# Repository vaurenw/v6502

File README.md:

A single-board computer built around a W65C02S 6502 CPU. It uses a Lattice ICE40HX4K FPGA as a custom chipset. The FPGA handles video, audio, keyboard, storage, and address decoding.

---

## Hardware

| Part | What it does |
|------|-------------|
| W65C02S | Main CPU, socketed |
| ICE40HX4K | FPGA chipset for video, audio, IO |
| 62256 SRAM | 32K RAM, socketed |
| AT28C256 EEPROM | 32K ROM, socketed |
| SN74LVC8T245 × 2 | 5V ↔ 3.3V level shifters for the data bus |
| FT230XS | USB-to-UART bridge for debug |
| MicroSD slot | SPI storage via FPGA |
| VGA connector | 640×480 @ 60Hz, resistor ladder DAC |
| PS/2 connector | Keyboard input, decoded in FPGA |

---

## Memory map

```
0x0000 – 0x7FFF   RAM
0x8000 – 0x8FFF   FPGA registers / VRAM window
0x9000 – 0xBFFF   Expansion
0xC000 – 0xFFFF   ROM
```

---

## Schematic sheets

```
V-6502.kicad_sch       root
├── Power.kicad_sch    USB-C, TVS, LDOs, decoupling
├── CPU.kicad_sch      W65C02S, clock, reset
├── Memory.kicad_sch   SRAM, EEPROM
├── LevelShift.kicad_sch   SN74LVC8T245 data bus bridges
├── FPGA.kicad_sch     ICE40HX4K, config flash, oscillator
├── VGA.kicad_sch      DE-15, RGB resistor ladder
├── PS2.kicad_sch      Mini-DIN-6, ESD, pull-ups
├── SD.kicad_sch       MicroSD slot, SPI
├── Audio.kicad_sch    Buzzer, 3.5mm jack
└── Debug.kicad_sch    FT230XS, UART header, test points
```

---

## Status

**Schematic done.** ERC passes clean.

**PCB layout in progress.** The power section is partially routed.

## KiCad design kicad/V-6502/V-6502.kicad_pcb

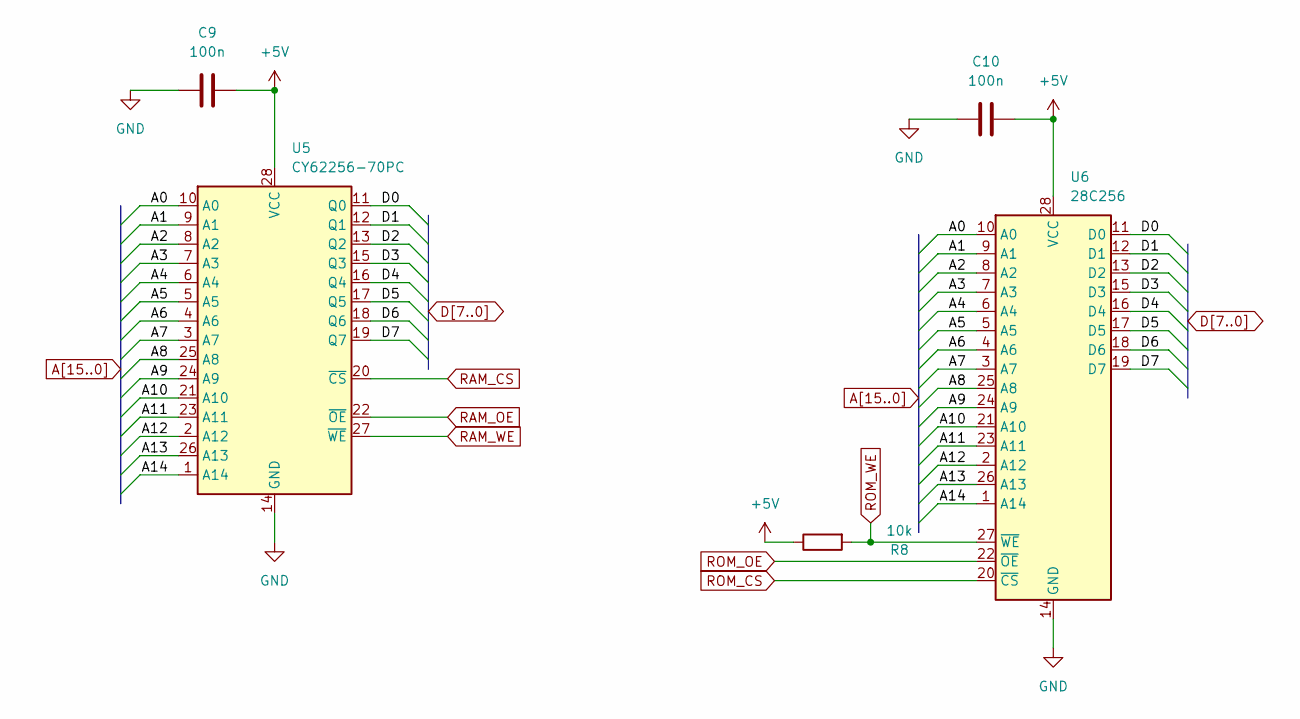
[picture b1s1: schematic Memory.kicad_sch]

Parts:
C9, C10: 100n; C_0805_2012Metric
R8: 10k; R_0402_1005Metric
U5: CY62256-70PC; DIP-28_W15.24mm_Socket
U6: 28C256; DIP-28_W15.24mm_Socket

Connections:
+5V: C9.2, C10.2, R8.1, U5.28 (VCC), U6.28 (VCC); also elsewhere on the board
A0: U5.10 (A0), U6.10 (A0); also elsewhere on the board
A1: U5.9 (A1), U6.9 (A1); also elsewhere on the board
A2: U5.8 (A2), U6.8 (A2); also elsewhere on the board
A3: U5.7 (A3), U6.7 (A3); also elsewhere on the board
A4: U5.6 (A4), U6.6 (A4); also elsewhere on the board
A5: U5.5 (A5), U6.5 (A5); also elsewhere on the board
A6: U5.4 (A6), U6.4 (A6); also elsewhere on the board
A7: U5.3 (A7), U6.3 (A7); also elsewhere on the board
A8: U5.25 (A8), U6.25 (A8); also elsewhere on the board
A9: U5.24 (A9), U6.24 (A9); also elsewhere on the board
A10: U5.21 (A10), U6.21 (A10); also elsewhere on the board
A11: U5.23 (A11), U6.23 (A11); also elsewhere on the board
A12: U5.2 (A12), U6.2 (A12); also elsewhere on the board
A13: U5.26 (A13), U6.26 (A13); also elsewhere on the board
A14: U5.1 (A14), U6.1 (A14); also elsewhere on the board
D0: U5.11 (Q0), U6.11 (D0); also elsewhere on the board
D1: U5.12 (Q1), U6.12 (D1); also elsewhere on the board
D2: U5.13 (Q2), U6.13 (D2); also elsewhere on the board
D3: U5.15 (Q3), U6.15 (D3); also elsewhere on the board
D4: U5.16 (Q4), U6.16 (D4); also elsewhere on the board
D5: U5.17 (Q5), U6.17 (D5); also elsewhere on the board
D6: U5.18 (Q6), U6.18 (D6); also elsewhere on the board
D7: U5.19 (Q7), U6.19 (D7); also elsewhere on the board
GND: C9.1, C10.1, U5.14 (GND), U6.14 (GND); also elsewhere on the board
RAM_CS: U5.20 (~CS); also elsewhere on the board
RAM_OE: U5.22 (~OE); also elsewhere on the board
RAM_WE: U5.27 (~WE); also elsewhere on the board
ROM_CS: U6.20 (~CS); also elsewhere on the board
ROM_OE: U6.22 (~OE); also elsewhere on the board
ROM_WE: R8.2, U6.27 (~WE); also elsewhere on the board

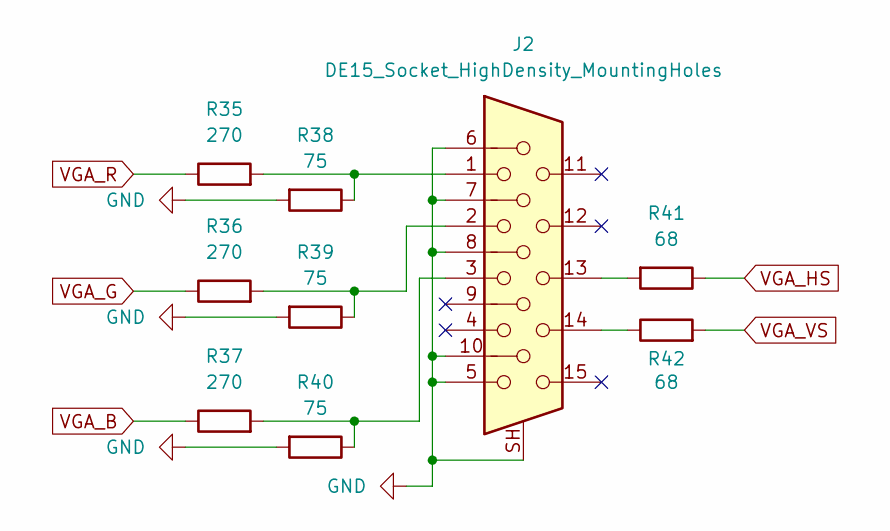
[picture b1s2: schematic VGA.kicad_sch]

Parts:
J2: DE15_Socket_HighDensity_MountingHoles; DSUB-15-HD_Socket_Vertical_P2.29x1.98mm_MountingHoles
R35, R36, R37: 270; R_0402_1005Metric
R38, R39, R40: 75; R_0402_1005Metric
R41, R42: 68; R_0402_1005Metric

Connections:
GND: J2.5, J2.6, J2.7, J2.8, J2.10, J2.SH, R38.2, R39.2, R40.2; also elsewhere on the board
unnamed: J2.1, R35.2, R38.1
unnamed: J2.2, R36.2, R39.1
unnamed: J2.3, R37.2, R40.1
unnamed: J2.13, R41.2
unnamed: J2.14, R42.1
VGA_B: R37.1; also elsewhere on the board
VGA_G: R36.1; also elsewhere on the board
VGA_HS: R41.1; also elsewhere on the board
VGA_R: R35.1; also elsewhere on the board
VGA_VS: R42.2; also elsewhere on the board

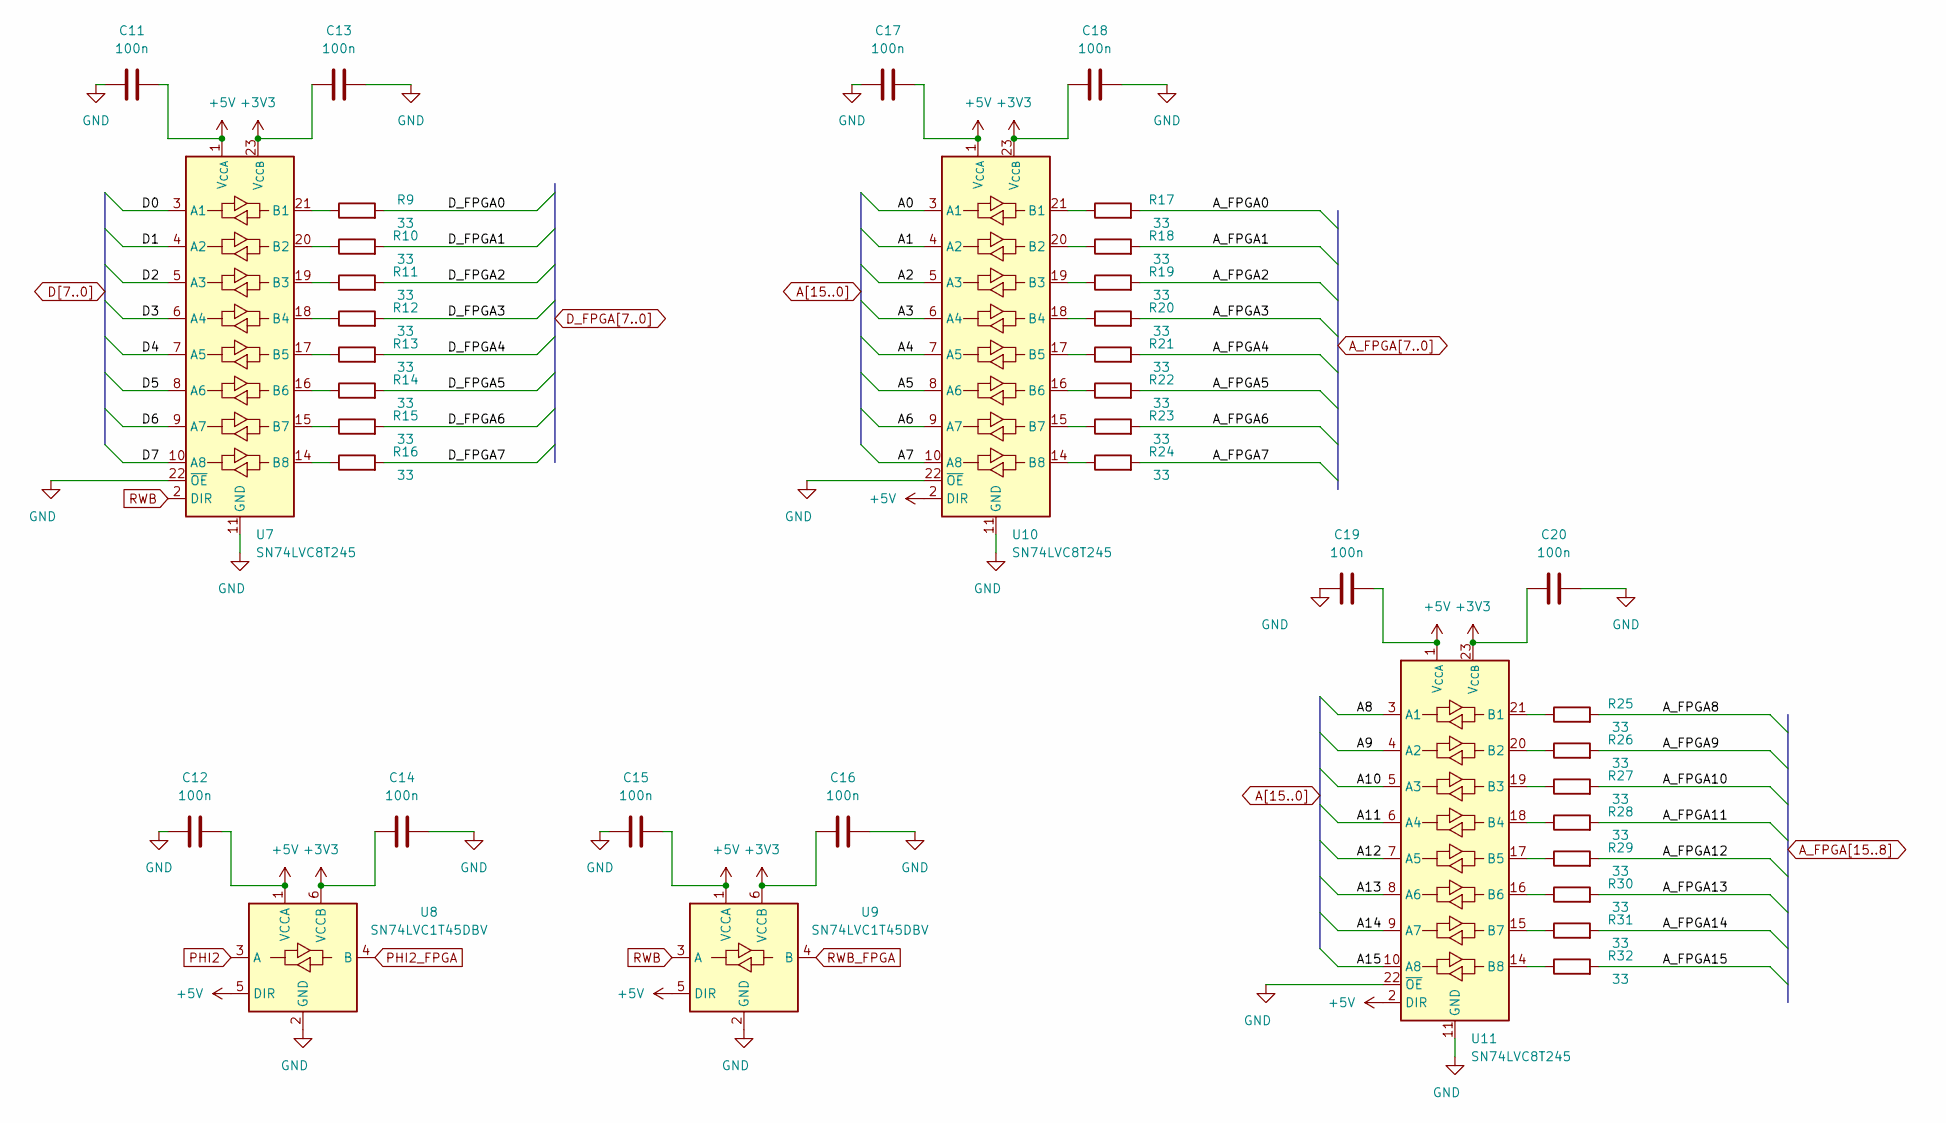
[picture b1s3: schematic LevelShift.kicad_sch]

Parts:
C11, C12, C13, C14, C15, C16, C17, C18, C19, C20: 100n; C_0805_2012Metric
R9, R10, R11, R12, R13, R14, R15, R16, R17, R18, R19, R20, R21, R22, R23, R24, R25, R26, R27, R28, R29, R30, R31, R32: 33; R_0402_1005Metric
U7, U10, U11: SN74LVC8T245; TSSOP-24_4.4x7.8mm_P0.65mm
U8, U9: SN74LVC1T45DBV; SOT-23-6

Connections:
+3V3: C13.2, C14.2, C16.2, C18.2, C20.2, U7.23 (V_{CCB}), U7.24 (V_{CCB}), U8.6 (VCCB), U9.6 (VCCB), U10.23 (V_{CCB}), U10.24 (V_{CCB}), U11.23 (V_{CCB}), U11.24 (V_{CCB}); also elsewhere on the board
+5V: C11.2, C12.2, C15.2, C17.2, C19.2, U7.1 (V_{CCA}), U8.1 (VCCA), U8.5 (DIR), U9.1 (VCCA), U9.5 (DIR), U10.1 (V_{CCA}), U10.2 (DIR), U11.1 (V_{CCA}), U11.2 (DIR); also elsewhere on the board
A0: U10.3 (A1); also elsewhere on the board
A1: U10.4 (A2); also elsewhere on the board
A2: U10.5 (A3); also elsewhere on the board
A3: U10.6 (A4); also elsewhere on the board
A4: U10.7 (A5); also elsewhere on the board
A5: U10.8 (A6); also elsewhere on the board
A6: U10.9 (A7); also elsewhere on the board
A7: U10.10 (A8); also elsewhere on the board
A8: U11.3 (A1); also elsewhere on the board
A9: U11.4 (A2); also elsewhere on the board
A10: U11.5 (A3); also elsewhere on the board
A11: U11.6 (A4); also elsewhere on the board
A12: U11.7 (A5); also elsewhere on the board
A13: U11.8 (A6); also elsewhere on the board
A14: U11.9 (A7); also elsewhere on the board
A15: U11.10 (A8); also elsewhere on the board
A_FPGA0: R17.2; also elsewhere on the board
A_FPGA1: R18.2; also elsewhere on the board
A_FPGA2: R19.2; also elsewhere on the board
A_FPGA3: R20.2; also elsewhere on the board
A_FPGA4: R21.2; also elsewhere on the board
A_FPGA5: R22.2; also elsewhere on the board
A_FPGA6: R23.2; also elsewhere on the board
A_FPGA7: R24.2; also elsewhere on the board
A_FPGA8: R25.2; also elsewhere on the board
A_FPGA9: R26.2; also elsewhere on the board
A_FPGA10: R27.2; also elsewhere on the board
A_FPGA11: R28.2; also elsewhere on the board
A_FPGA12: R29.2; also elsewhere on the board
A_FPGA13: R30.2; also elsewhere on the board
A_FPGA14: R31.2; also elsewhere on the board
A_FPGA15: R32.2; also elsewhere on the board
D0: U7.3 (A1); also elsewhere on the board
D1: U7.4 (A2); also elsewhere on the board
D2: U7.5 (A3); also elsewhere on the board
D3: U7.6 (A4); also elsewhere on the board
D4: U7.7 (A5); also elsewhere on the board
D5: U7.8 (A6); also elsewhere on the board
D6: U7.9 (A7); also elsewhere on the board
D7: U7.10 (A8); also elsewhere on the board
D_FPGA0: R9.2; also elsewhere on the board
D_FPGA1: R10.2; also elsewhere on the board
D_FPGA2: R11.2; also elsewhere on the board
D_FPGA3: R12.2; also elsewhere on the board
D_FPGA4: R13.2; also elsewhere on the board
D_FPGA5: R14.2; also elsewhere on the board
D_FPGA6: R15.2; also elsewhere on the board
D_FPGA7: R16.2; also elsewhere on the board
GND: C11.1, C12.1, C13.1, C14.1, C15.1, C16.1, C17.1, C18.1, C19.1, C20.1, U7.11 (GND), U7.12 (GND), U7.13 (GND), U7.22 (~OE), U8.2 (GND), U9.2 (GND), U10.11 (GND), U10.12 (GND), U10.13 (GND), U10.22 (~OE), U11.11 (GND), U11.12 (GND), U11.13 (GND), U11.22 (~OE); also elsewhere on the board
unnamed: R9.1, U7.21 (B1)
unnamed: R10.1, U7.20 (B2)
unnamed: R11.1, U7.19 (B3)
unnamed: R12.1, U7.18 (B4)
unnamed: R13.1, U7.17 (B5)
unnamed: R14.1, U7.16 (B6)
unnamed: R15.1, U7.15 (B7)
unnamed: R16.1, U7.14 (B8)
unnamed: R17.1, U10.21 (B1)
unnamed: R18.1, U10.20 (B2)
unnamed: R19.1, U10.19 (B3)
unnamed: R20.1, U10.18 (B4)
unnamed: R21.1, U10.17 (B5)
unnamed: R22.1, U10.16 (B6)
unnamed: R23.1, U10.15 (B7)
unnamed: R24.1, U10.14 (B8)
unnamed: R25.1, U11.21 (B1)
unnamed: R26.1, U11.20 (B2)
unnamed: R27.1, U11.19 (B3)
unnamed: R28.1, U11.18 (B4)
unnamed: R29.1, U11.17 (B5)
unnamed: R30.1, U11.16 (B6)
unnamed: R31.1, U11.15 (B7)
unnamed: R32.1, U11.14 (B8)
PHI2: U8.3 (A); also elsewhere on the board
PHI2_FPGA: U8.4 (B); also elsewhere on the board
RWB: U7.2 (DIR), U9.3 (A); also elsewhere on the board
RWB_FPGA: U9.4 (B); also elsewhere on the board

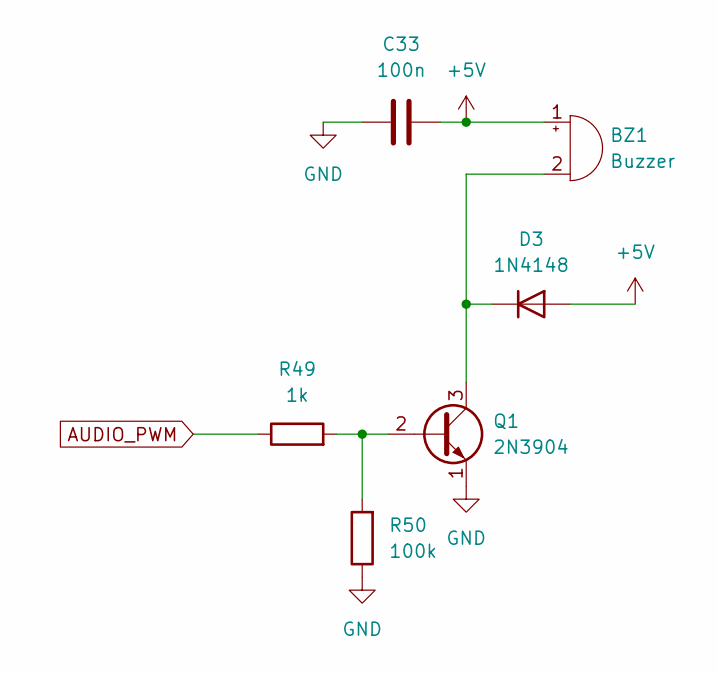
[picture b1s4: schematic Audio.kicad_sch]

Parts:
BZ1: Buzzer; Buzzer_15x7.5RM7.6
C33: 100n; C_0805_2012Metric
D3: 1N4148; D_DO-35_SOD27_P7.62mm_Horizontal
Q1: 2N3904; TO-92_Inline
R49: 1k; R_0402_1005Metric
R50: 100k; R_0402_1005Metric

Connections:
+5V: BZ1.1 (+), C33.2, D3.2 (A); also elsewhere on the board
AUDIO_PWM: R49.1; also elsewhere on the board
GND: C33.1, Q1.1 (E), R50.1; also elsewhere on the board
unnamed: BZ1.2 (-), D3.1 (K), Q1.3 (C)
unnamed: Q1.2 (B), R49.2, R50.2

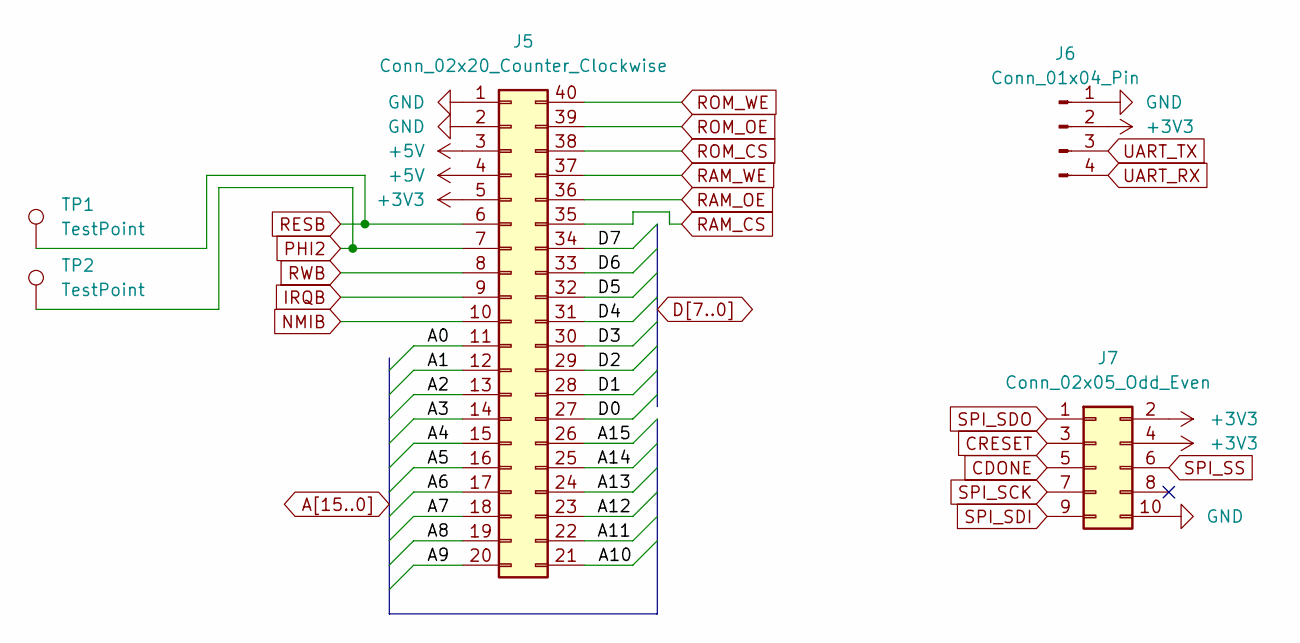
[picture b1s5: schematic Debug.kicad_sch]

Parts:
J5: Conn_02x20_Counter_Clockwise; PinSocket_2x20_P2.54mm_Vertical
J6: Conn_01x04_Pin; PinHeader_1x04_P2.54mm_Vertical
J7: Conn_02x05_Odd_Even; IDC-Header_2x05_P2.54mm_Vertical
TP1, TP2: TestPoint; TestPoint_Pad_D1.0mm

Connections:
+3V3: J5.5, J6.2, J7.2, J7.4; also elsewhere on the board
+5V: J5.3, J5.4; also elsewhere on the board
A0: J5.11; also elsewhere on the board
A1: J5.12; also elsewhere on the board
A2: J5.13; also elsewhere on the board
A3: J5.14; also elsewhere on the board
A4: J5.15; also elsewhere on the board
A5: J5.16; also elsewhere on the board
A6: J5.17; also elsewhere on the board
A7: J5.18; also elsewhere on the board
A8: J5.19; also elsewhere on the board
A9: J5.20; also elsewhere on the board
A10: J5.21; also elsewhere on the board
A11: J5.22; also elsewhere on the board
A12: J5.23; also elsewhere on the board
A13: J5.24; also elsewhere on the board
A14: J5.25; also elsewhere on the board
A15: J5.26; also elsewhere on the board
CDONE: J7.5; also elsewhere on the board
CRESET: J7.3; also elsewhere on the board
D0: J5.27; also elsewhere on the board
D1: J5.28; also elsewhere on the board
D2: J5.29; also elsewhere on the board
D3: J5.30; also elsewhere on the board
D4: J5.31; also elsewhere on the board
D5: J5.32; also elsewhere on the board
D6: J5.33; also elsewhere on the board
D7: J5.34; also elsewhere on the board
GND: J5.1, J5.2, J6.1, J7.10; also elsewhere on the board
IRQB: J5.9; also elsewhere on the board
NMIB: J5.10; also elsewhere on the board
PHI2: J5.7, TP2.1 (1_1); also elsewhere on the board
RAM_CS: J5.35; also elsewhere on the board
RAM_OE: J5.36; also elsewhere on the board
RAM_WE: J5.37; also elsewhere on the board
RESB: J5.6, TP1.1 (1_1); also elsewhere on the board
ROM_CS: J5.38; also elsewhere on the board
ROM_OE: J5.39; also elsewhere on the board
ROM_WE: J5.40; also elsewhere on the board
RWB: J5.8; also elsewhere on the board
SPI_SCK: J7.7; also elsewhere on the board
SPI_SDI: J7.9; also elsewhere on the board
SPI_SDO: J7.1; also elsewhere on the board
SPI_SS: J7.6; also elsewhere on the board
UART_RX: J6.4; also elsewhere on the board
UART_TX: J6.3; also elsewhere on the board

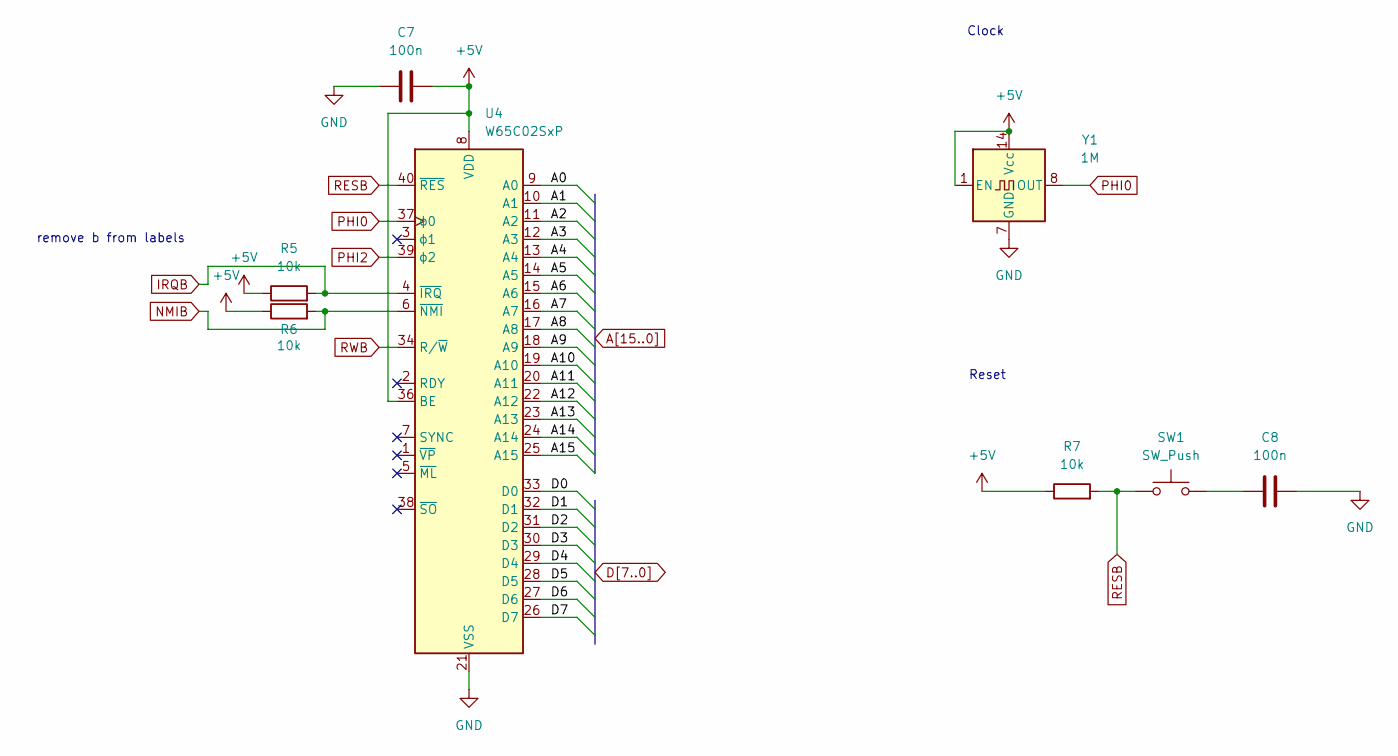
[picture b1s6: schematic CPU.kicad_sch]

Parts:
C7, C8: 100n; C_0805_2012Metric
R5, R6, R7: 10k; R_0402_1005Metric
SW1: SW_Push; SW_PUSH_6mm
U4: W65C02SxP; DIP-40_W15.24mm_Socket
Y1: 1M; Oscillator_DIP-14

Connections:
+5V: C7.2, R5.1, R6.1, R7.1, U4.8 (VDD), U4.36 (BE), Y1.1 (EN), Y1.14 (Vcc); also elsewhere on the board
A0: U4.9 (A0); also elsewhere on the board
A1: U4.10 (A1); also elsewhere on the board
A2: U4.11 (A2); also elsewhere on the board
A3: U4.12 (A3); also elsewhere on the board
A4: U4.13 (A4); also elsewhere on the board
A5: U4.14 (A5); also elsewhere on the board
A6: U4.15 (A6); also elsewhere on the board
A7: U4.16 (A7); also elsewhere on the board
A8: U4.17 (A8); also elsewhere on the board
A9: U4.18 (A9); also elsewhere on the board
A10: U4.19 (A10); also elsewhere on the board
A11: U4.20 (A11); also elsewhere on the board
A12: U4.22 (A12); also elsewhere on the board
A13: U4.23 (A13); also elsewhere on the board
A14: U4.24 (A14); also elsewhere on the board
A15: U4.25 (A15); also elsewhere on the board
D0: U4.33 (D0); also elsewhere on the board
D1: U4.32 (D1); also elsewhere on the board
D2: U4.31 (D2); also elsewhere on the board
D3: U4.30 (D3); also elsewhere on the board
D4: U4.29 (D4); also elsewhere on the board
D5: U4.28 (D5); also elsewhere on the board
D6: U4.27 (D6); also elsewhere on the board
D7: U4.26 (D7); also elsewhere on the board
GND: C7.1, C8.2, U4.21 (VSS), Y1.7 (GND); also elsewhere on the board
IRQB: R5.2, U4.4 (~IRQ); also elsewhere on the board
NMIB: R6.2, U4.6 (~NMI); also elsewhere on the board
unnamed: C8.1, SW1.2
PHI0: U4.37 (ϕ0), Y1.8 (OUT)
PHI2: U4.39 (ϕ2); also elsewhere on the board
RESB: R7.2, SW1.1, U4.40 (~RES); also elsewhere on the board
RWB: U4.34 (R/~W); also elsewhere on the board

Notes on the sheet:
Reset
remove b from labels
Clock

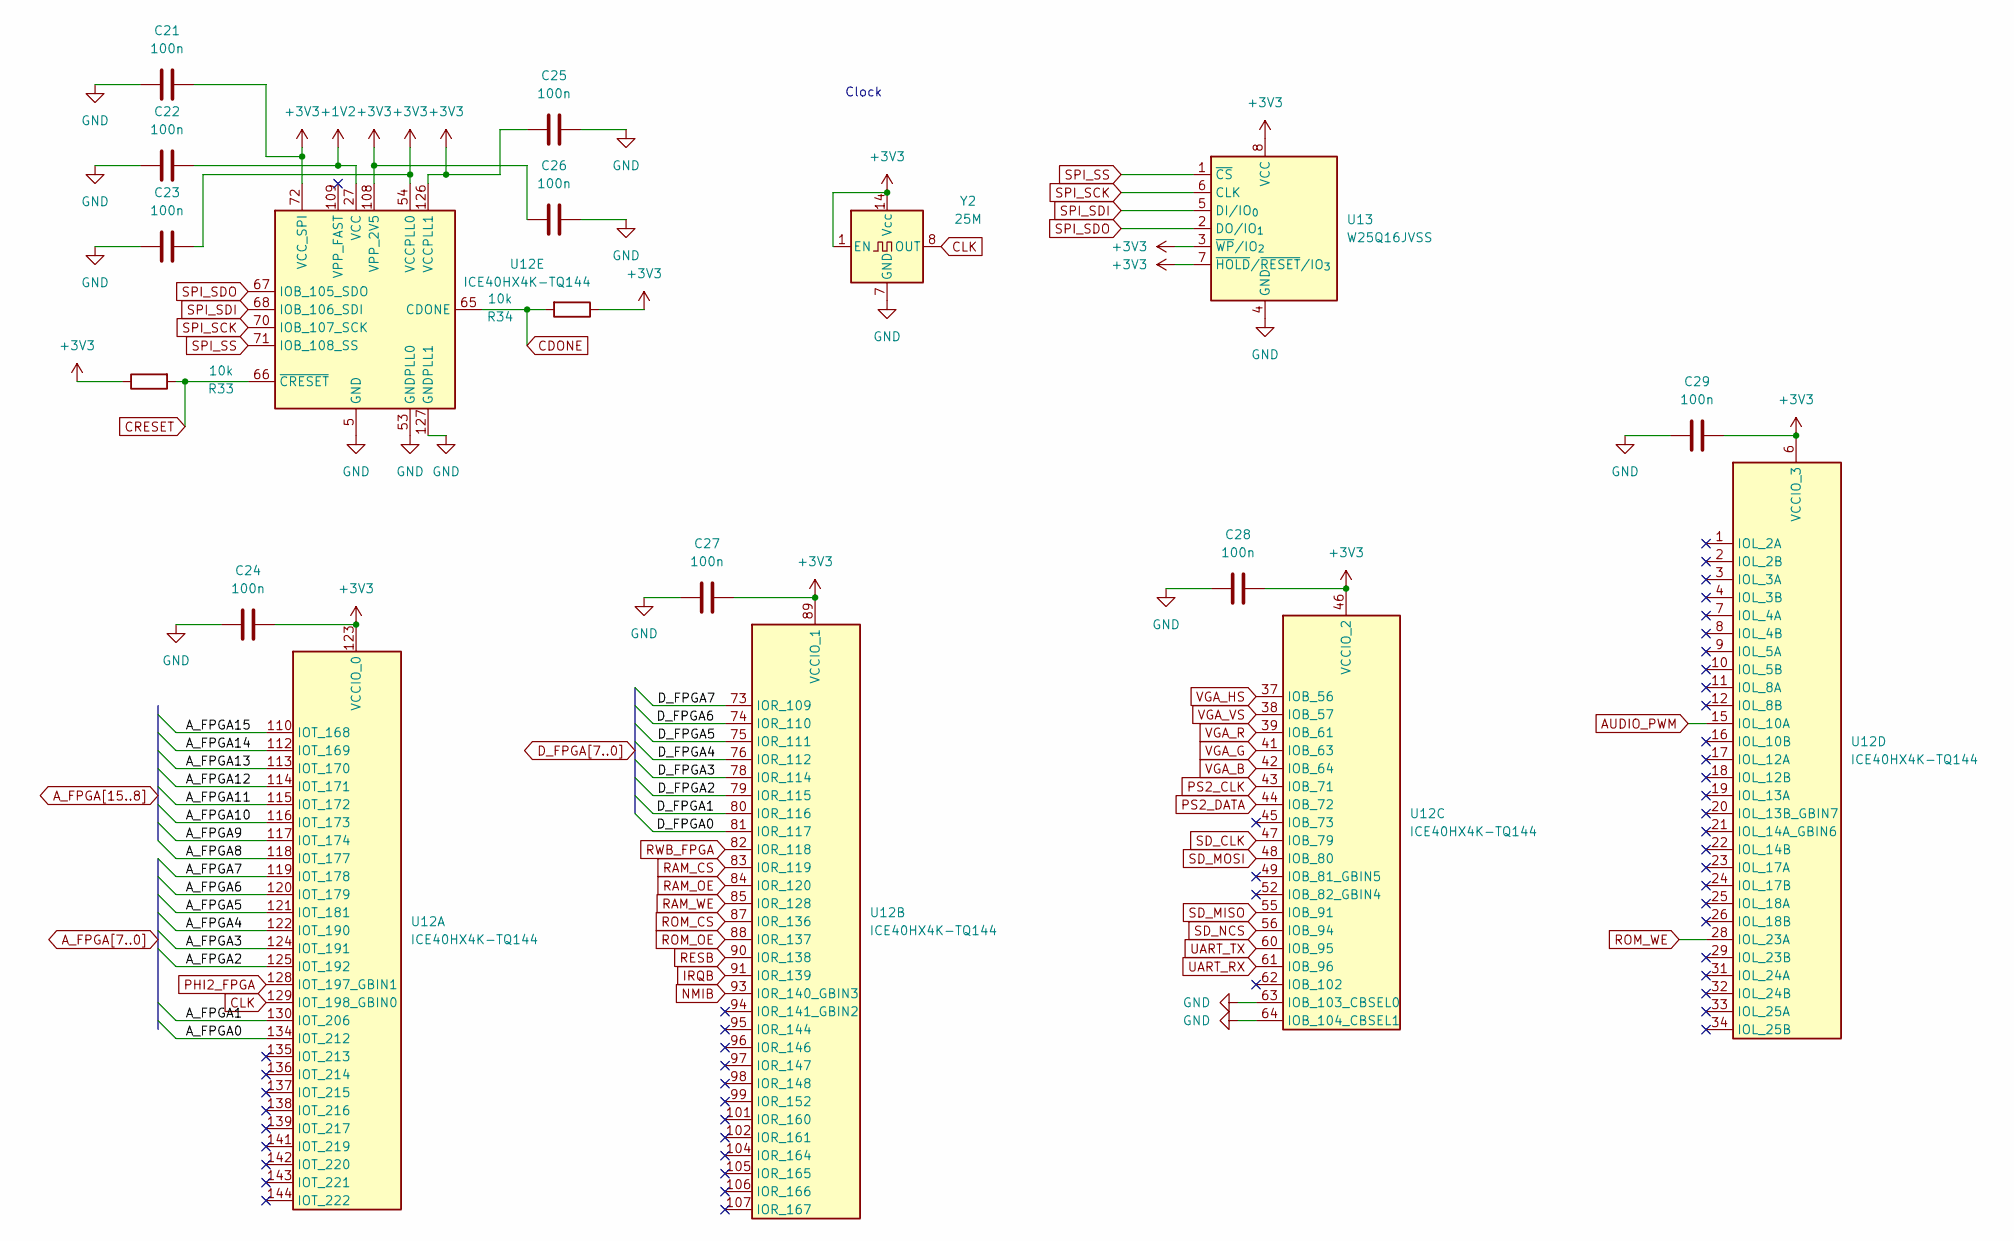
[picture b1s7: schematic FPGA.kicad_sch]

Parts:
C21, C22, C23, C24, C25, C26, C27, C28, C29: 100n; C_0805_2012Metric
R33, R34: 10k; R_0402_1005Metric
U12: ICE40HX4K-TQ144; TQFP-144_20x20mm_P0.5mm
U13: W25Q16JVSS; SOIC-8_5.3x5.3mm_P1.27mm
Y2: 25M; Oscillator_DIP-14

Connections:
+1V2: C22.2, U12.27 (VCC), U12.40 (VCC), U12.92 (VCC), U12.111 (VCC); also elsewhere on the board
+3V3: C21.2, C23.2, C24.2, C25.2, C26.2, C27.2, C28.2, C29.2, R33.1, R34.1, U12.6 (VCCIO_3), U12.30 (VCCIO_3), U12.46 (VCCIO_2), U12.54 (VCCPLL0), U12.57 (VCCIO_2), U12.72 (VCC_SPI), U12.89 (VCCIO_1), U12.100 (VCCIO_1), U12.108 (VPP_2V5), U12.123 (VCCIO_0), U12.126 (VCCPLL1), U12.131 (VCCIO_0), U13.3 (~WP/IO_{2}), U13.7 (~HOLD/~RESET/IO_{3}), U13.8 (VCC), Y2.1 (EN), Y2.14 (Vcc); also elsewhere on the board
AUDIO_PWM: U12.15 (IOL_10A); also elsewhere on the board
A_FPGA0: U12.134 (IOT_212); also elsewhere on the board
A_FPGA1: U12.130 (IOT_206); also elsewhere on the board
A_FPGA2: U12.125 (IOT_192); also elsewhere on the board
A_FPGA3: U12.124 (IOT_191); also elsewhere on the board
A_FPGA4: U12.122 (IOT_190); also elsewhere on the board
A_FPGA5: U12.121 (IOT_181); also elsewhere on the board
A_FPGA6: U12.120 (IOT_179); also elsewhere on the board
A_FPGA7: U12.119 (IOT_178); also elsewhere on the board
A_FPGA8: U12.118 (IOT_177); also elsewhere on the board
A_FPGA9: U12.117 (IOT_174); also elsewhere on the board
A_FPGA10: U12.116 (IOT_173); also elsewhere on the board
A_FPGA11: U12.115 (IOT_172); also elsewhere on the board
A_FPGA12: U12.114 (IOT_171); also elsewhere on the board
A_FPGA13: U12.113 (IOT_170); also elsewhere on the board
A_FPGA14: U12.112 (IOT_169); also elsewhere on the board
A_FPGA15: U12.110 (IOT_168); also elsewhere on the board
CDONE: R34.2, U12.65 (CDONE); also elsewhere on the board
CLK: U12.129 (IOT_198_GBIN0), Y2.8 (OUT)
CRESET: R33.2, U12.66 (~CRESET); also elsewhere on the board
D_FPGA0: U12.81 (IOR_117); also elsewhere on the board
D_FPGA1: U12.80 (IOR_116); also elsewhere on the board
D_FPGA2: U12.79 (IOR_115); also elsewhere on the board
D_FPGA3: U12.78 (IOR_114); also elsewhere on the board
D_FPGA4: U12.76 (IOR_112); also elsewhere on the board
D_FPGA5: U12.75 (IOR_111); also elsewhere on the board
D_FPGA6: U12.74 (IOR_110); also elsewhere on the board
D_FPGA7: U12.73 (IOR_109); also elsewhere on the board
GND: C21.1, C22.1, C23.1, C24.1, C25.1, C26.1, C27.1, C28.1, C29.1, U12.5 (GND), U12.13 (GND), U12.14 (GND), U12.53 (GNDPLL0), U12.59 (GND), U12.63 (IOB_103_CBSEL0), U12.64 (IOB_104_CBSEL1), U12.69 (GND), U12.86 (GND), U12.103 (GND), U12.127 (GNDPLL1), U12.132 (GND), U12.140 (GND), U13.4 (GND), Y2.7 (GND); also elsewhere on the board
IRQB: U12.91 (IOR_139); also elsewhere on the board
NMIB: U12.93 (IOR_140_GBIN3); also elsewhere on the board
PHI2_FPGA: U12.128 (IOT_197_GBIN1); also elsewhere on the board
PS2_CLK: U12.43 (IOB_71); also elsewhere on the board
PS2_DATA: U12.44 (IOB_72); also elsewhere on the board
RAM_CS: U12.83 (IOR_119); also elsewhere on the board
RAM_OE: U12.84 (IOR_120); also elsewhere on the board
RAM_WE: U12.85 (IOR_128); also elsewhere on the board
RESB: U12.90 (IOR_138); also elsewhere on the board
ROM_CS: U12.87 (IOR_136); also elsewhere on the board
ROM_OE: U12.88 (IOR_137); also elsewhere on the board
ROM_WE: U12.28 (IOL_23A); also elsewhere on the board
RWB_FPGA: U12.82 (IOR_118); also elsewhere on the board
SD_CLK: U12.47 (IOB_79); also elsewhere on the board
SD_MISO: U12.55 (IOB_91); also elsewhere on the board
SD_MOSI: U12.48 (IOB_80); also elsewhere on the board
SD_NCS: U12.56 (IOB_94); also elsewhere on the board
SPI_SCK: U12.70 (IOB_107_SCK), U13.6 (CLK); also elsewhere on the board
SPI_SDI: U12.68 (IOB_106_SDI), U13.5 (DI/IO_{0}); also elsewhere on the board
SPI_SDO: U12.67 (IOB_105_SDO), U13.2 (DO/IO_{1}); also elsewhere on the board
SPI_SS: U12.71 (IOB_108_SS), U13.1 (~CS); also elsewhere on the board
UART_RX: U12.61 (IOB_96); also elsewhere on the board
UART_TX: U12.60 (IOB_95); also elsewhere on the board
VGA_B: U12.42 (IOB_64); also elsewhere on the board
VGA_G: U12.41 (IOB_63); also elsewhere on the board
VGA_HS: U12.37 (IOB_56); also elsewhere on the board
VGA_R: U12.39 (IOB_61); also elsewhere on the board
VGA_VS: U12.38 (IOB_57); also elsewhere on the board

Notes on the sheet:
Clock

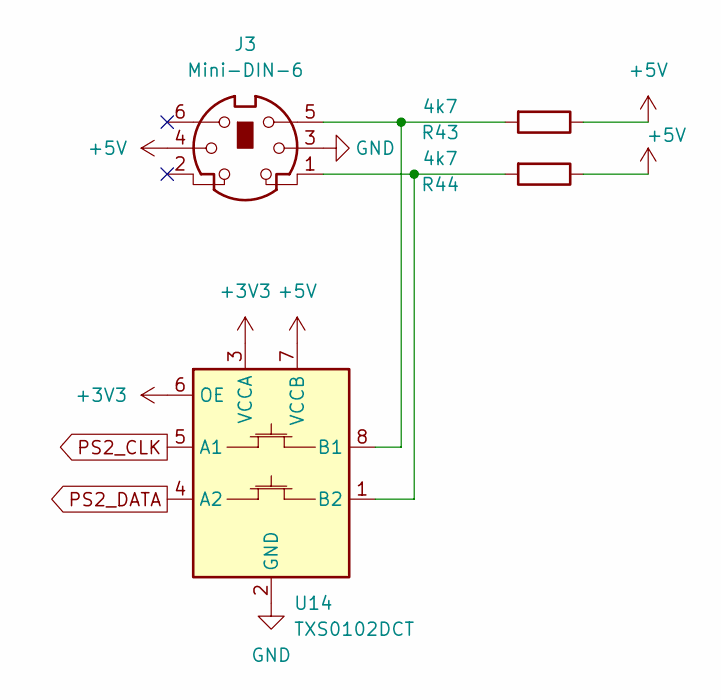
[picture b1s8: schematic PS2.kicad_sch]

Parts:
J3: Mini-DIN-6; Connector_Mini-DIN_Female_6Pin_2rows
R43, R44: 4k7; R_0402_1005Metric
U14: TXS0102DCT; SSOP-8_2.95x2.8mm_P0.65mm

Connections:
+3V3: U14.3 (VCCA), U14.6 (OE); also elsewhere on the board
+5V: J3.4, R43.1, R44.1, U14.7 (VCCB); also elsewhere on the board
GND: J3.3, U14.2 (GND); also elsewhere on the board
unnamed: J3.5, R43.2, U14.8 (B1)
unnamed: J3.1, R44.2, U14.1 (B2)
PS2_CLK: U14.5 (A1); also elsewhere on the board
PS2_DATA: U14.4 (A2); also elsewhere on the board

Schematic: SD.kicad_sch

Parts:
C30, C31, C32: 100n; C_0805_2012Metric
J4: Micro_SD_Card; microSD_HC_Molex_47219-2001
R45, R46, R47: 33; R_0402_1005Metric
R48: 10k; R_0402_1005Metric
U15: FT230XS; SSOP-16_3.9x4.9mm_P0.635mm

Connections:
+3V3: C30.2, C31.2, C32.2, J4.4 (VDD), R48.1, U15.3 (VCCIO), U15.12 (VCC); also elsewhere on the board
GND: C30.1, C31.1, C32.1, J4.6 (VSS), J4.SH (SHIELD), U15.5 (GND), U15.13 (GND); also elsewhere on the board
unnamed: J4.5 (CLK), R47.2
unnamed: J4.3 (CMD), R46.2
unnamed: J4.2 (DAT3/CD), R45.2
unnamed: R48.2, U15.11 (~RESET)
SD_CLK: R47.1; also elsewhere on the board
SD_MISO: J4.7 (DAT0); also elsewhere on the board
SD_MOSI: R46.1; also elsewhere on the board
SD_NCS: R45.1; also elsewhere on the board
UART_RX: U15.1 (TXD); also elsewhere on the board
UART_TX: U15.4 (RXD); also elsewhere on the board
USB_D+: U15.8 (USBDP); also elsewhere on the board
USB_D-: U15.9 (USBDM); also elsewhere on the board

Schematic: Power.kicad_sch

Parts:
C1, C2, C3, C4, C5, C6: 4u7; C_0805_2012Metric
D1: PESD5V0L1ULD; D_SOD-882D
D2: LED; LED_0805_2012Metric
J1: USB_C_Receptacle_USB2.0_16P; USB_C_Receptacle_GCT_USB4085
R1, R2: 5k1; R_0402_1005Metric
R3: 0R; R_0402_1005Metric
R4: 2k; R_0402_1005Metric
U1: USBLC6-2SC6; SOT-23-6
U2: AP2112K-3.3; SOT-23-5
U3: AP2112K-1.2; SOT-23-5

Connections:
+1V2: C6.1, U3.5 (VOUT); also elsewhere on the board
+3V3: C5.1, U2.5 (VOUT); also elsewhere on the board
+5V: C2.1, C3.1, C4.1, R3.2, R4.2, U2.1 (VIN), U2.3 (EN), U3.1 (VIN), U3.3 (EN); also elsewhere on the board
/Power/D+: J1.A6 (D+), J1.B6 (D+), U1.3 (I/O2)
/Power/D-: J1.A7 (D-), J1.B7 (D-), U1.1 (I/O1)
GND: C1.2, C2.2, C3.2, C4.2, C5.2, C6.2, D1.2 (A), D2.1 (K), J1.A1 (GND), J1.A12 (GND), J1.B1 (GND), J1.B12 (GND), J1.SH (SHIELD), R1.2, R2.2, U1.2 (GND), U2.2 (GND), U3.2 (GND); also elsewhere on the board
unnamed: D2.2 (A), R4.1
unnamed: J1.A5 (CC1), R2.1
unnamed: J1.B5 (CC2), R1.1
USB_D+: U1.4 (I/O2); also elsewhere on the board
USB_D-: U1.6 (I/O1); also elsewhere on the board
VBUS: C1.1, D1.1 (K), J1.A4 (VBUS), J1.A9 (VBUS), J1.B4 (VBUS), J1.B9 (VBUS), R3.1

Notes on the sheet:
3.3V LDO
1.2V LDO
Input Power and USBC
Power on LED

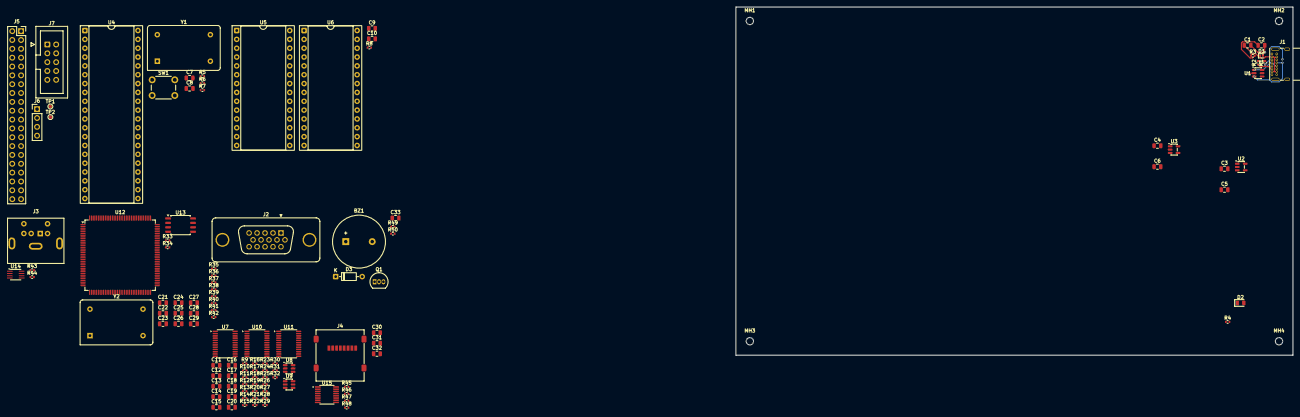
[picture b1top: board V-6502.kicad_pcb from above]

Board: 2 copper layers, 160.0 x 100.0 mm, 119 parts (0 on the bottom side), 133 nets.

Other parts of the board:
MH1, MH2, MH3, MH4: MountingHole_2.1mm

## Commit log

2026-06-01 first
